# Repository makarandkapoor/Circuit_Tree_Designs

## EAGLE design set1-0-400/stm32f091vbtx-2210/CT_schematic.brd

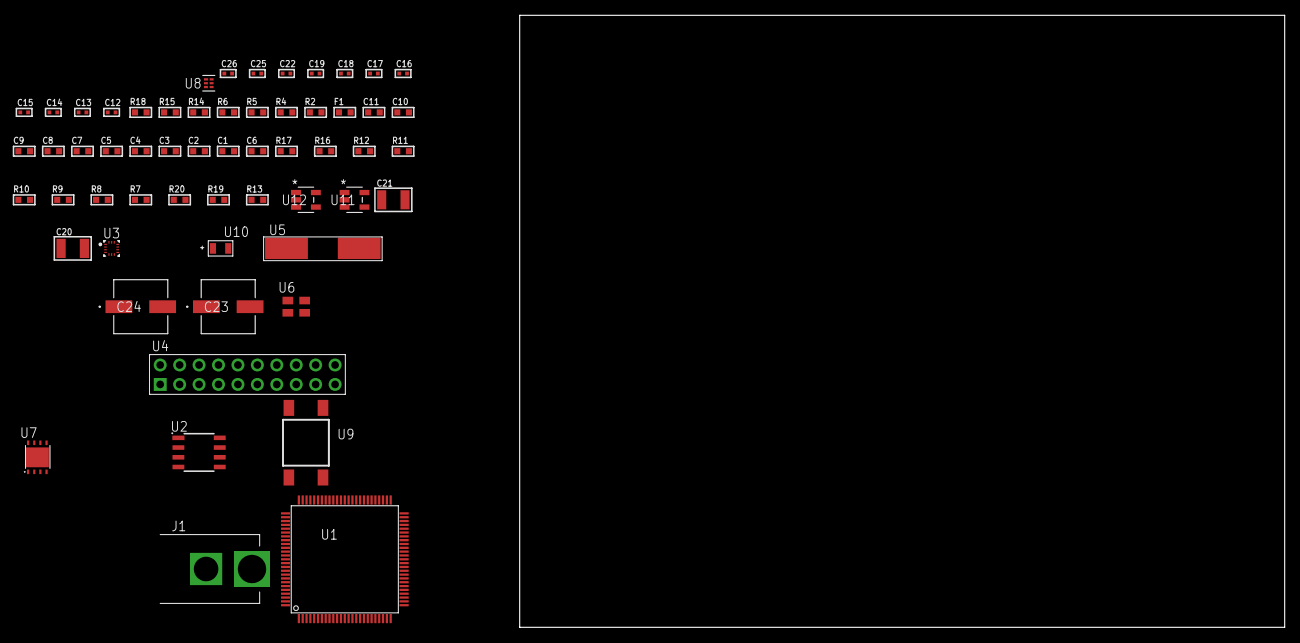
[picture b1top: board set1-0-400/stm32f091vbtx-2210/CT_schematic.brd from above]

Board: 2 copper layers, 100.0 x 80.0 mm, 58 parts (0 on the bottom side), 28 nets, no tracks yet.

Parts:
C1, C11: 1e-06; C0603
C2, C3, C4, C5, C7, C8, C9: 1e-07; C0603
C6: 4.7e-06; C0603
C10: 1e-08; C0603
C12, C13: 1e-11; C0402
C14, C18, C19, C25, C26: 1e-08; C0402
C15, C16, C17, C22: 1e-07; C0402
C20, C21: 1e-05; C1210
C23, C24: 0.0001; EXV-9H
F1: 240.0; L0603
J1: PJ-037B; PJ-037B_PACKAGE
R2, R15: 1000.0; R0603
R4: 4700.0; R0603
R5, R6: 2200.0; R0603
R7, R8, R9, R10, R11, R12, R16, R17: 10000.0; R0603
R13: 100000.0; R0603
R14: 2231.0; R0603
R18: 9100.0; R0603
R19: 680000.0; R0603
R20: 120000.0; R0603
U1: stm32f091vbt6; LQFP100
U2: AT25512N-SH-T; SOIC-8
U3: BMC150; LGA14R35P5X6_200X200X100
U4: TST-110-05-T-D-RA
U5: ABLS-25.000MHZ-B2F-T
U6: ASEK-32.768KHz-ECST; ASEK
U7: LP3878SDX-ADJ/NOPB; WSON-8
U8: TPS3895ADRYR; SON-6
U9: 4-1437565-2; SW_4-1437565-2
U10: Q65110A2395; LGM67K-G1J2-24-Z
U11, U12: nc7sz125m5x; NC7SZ125M5X

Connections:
CLK_CRYSTAL_U1_12: C12.1, U1.12, U5.1
CLK_CRYSTAL_U1_13: C13.1, U1.13, U5.2
CLK_U1_8: U1.8, U6.3
GND: C1.2, C2.2, C3.2, C4.2, C5.2, C6.2, C7.2, C8.2, C9.2, C10.2, C11.2, C12.2, C13.2, C14.2, C15.2, C16.2, C17.2, C18.2, C19.2, C20.2, C21.2, C22.2, C23.2, C24.2, C25.2, C26.2, J1.2, R2.2, R7.2, R15.2, R18.2, R20.2, U1.20, U1.27, U1.49, U1.74, U1.99, U2.4, U3.1, U3.6, U3.7, U3.9, U4.4, U4.6, U4.8, U4.10, U4.12, U4.14, U4.16, U4.18, U4.20, U6.2, U7.3, U7.PAD, U8.2, U10.C, U11.2, U11.3, U12.1, U12.3
NET_U1_14: R4.1, U1.14, U12.4
NET_U1_21: C10.1, C11.1, F1.1, U1.21
NET_U1_68: R5.1, U1.68, U3.11
NET_U1_69: R6.1, U1.69, U3.14
NET_U1_94: R7.1, U1.94
NET_U1_98: U9.3, U9.4
NET_U2_3: R8.1, U2.3
NET_U2_7: R10.1, U2.7
NET_U7_1: C19.1, U7.1
NET_U7_6: R14.2, R15.1, U7.6
NET_U7_8: R13.1, U7.8
NET_U8_1: R17.1, R18.1, U8.1
NET_U8_3: R19.2, R20.1, U8.3
NET_U8_4: R16.1, U8.4, U11.4, U12.2
NET_U9_1: R2.1, U9.1, U9.2
PROC_SPI1_MISO: U1.31, U2.2
PROC_SPI1_MOSI: U1.32, U2.5
PROC_SPI1_NSS: R9.1, U1.29, U2.1
PROC_SPI1_SCK: U1.30, U2.6
PROC_SYS_SWCLK: U1.76, U4.9
PROC_SYS_SWDIO: U1.72, U4.7
RST_OUT_U4_SRESET_B: R12.1, U4.15, U11.1
VCC_S1_14V6: C20.1, C23.1, C24.1, J1.1, R13.2, U7.4
VCC_TIER1_3V3: C1.1, C2.1, C3.1, C4.1, C5.1, C6.1, C7.1, C8.1, C9.1, C14.1, C15.1, C16.1, C17.1, C18.1, C21.1, C22.1, C25.1, C26.1, F1.2, R4.2, R5.2, R6.2, R8.2, R9.2, R10.2, R11.1, R11.2, R12.2, R14.1, R16.2, R17.2, R19.1, U1.6, U1.28, U1.50, U1.75, U1.100, U2.8, U3.8, U3.10, U3.12, U3.13, U4.1, U6.4, U7.5, U8.6, U11.5, U12.5

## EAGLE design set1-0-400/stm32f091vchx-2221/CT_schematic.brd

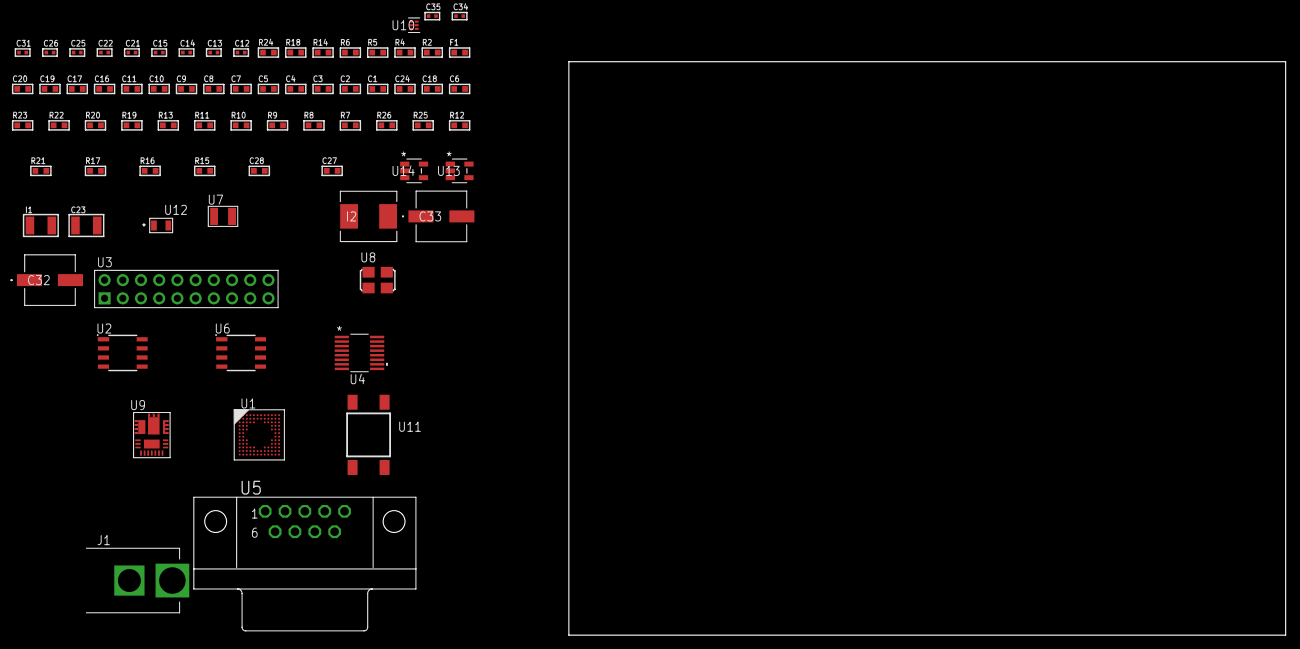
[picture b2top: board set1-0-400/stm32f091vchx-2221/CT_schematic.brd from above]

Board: 2 copper layers, 100.0 x 80.0 mm, 75 parts (0 on the bottom side), 45 nets, no tracks yet.

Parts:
C1, C11, C16, C17, C19, C20: 1e-06; C0603
C2, C3, C4, C5, C7, C8, C9: 1e-07; C0603
C6: 4.7e-06; C0603
C10: 1e-08; C0603
C12, C13: 1e-11; C0402
C14, C21, C22, C34, C35: 1e-08; C0402
C15, C25, C26, C31: 1e-07; C0402
C18: 2.2e-07; C0603
C23: 0.0001; C1210
C24: 2.2e-06; C0603
C27: 8.6971073877236e-09; R0603
C28: 2.9649229730876e-07; R0603
C32, C33: 0.0001; EXV-9H
F1: 240.0; L0603
I1: 1e-05; L1210
I2: 6.8e-07; IND25X25CZ
J1: PJ-037B; PJ-037B_PACKAGE
R2: 1000.0; R0603
R4: 4700.0; R0603
R5, R6: 2200.0; R0603
R7, R8, R9, R10, R11, R13, R22, R23: 10000.0; R0603
R12: 100000.0; R0603
R14: 0.1; R0603
R15: 4030.2416170974; R0603
R16: 719.68600305311; R0603
R17: 58.613333333333; R0603
R18: 130.0; R0603
R19: 39000.0; R0603
R20: 49900.0; R0603
R21: 5147.5789473684; R0603
R24: 9100.0; R0603
R25: 680000.0; R0603
R26: 120000.0; R0603
U1: stm32f091vch6; UFBGA100
U2: AT25M01-SSHM-T; SOIC-8
U3: TST-110-05-T-D-RA
U4: LTC2804CGN-1#PBF; SSOP-16
U5: 182-009-113R531; 182-009-MALE
U6: M24M02-DRMN6TP; SOIC-8
U7: ABS07-32.768KHZ-7-T
U8: ASFL1-25MHZ-NCS; ASFL1
U9: IR3899MTR1PBF
U10: TPS3895ADRYR; SON-6
U11: 4-1437565-2; SW_4-1437565-2
U12: Q65110A2395; LGM67K-G1J2-24-Z
U13, U14: nc7sz125m5x; NC7SZ125M5X

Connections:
CLK_CRYSTAL_U1_D1: C12.1, U1.D1, U7.1
CLK_CRYSTAL_U1_E1: C13.1, U1.E1, U7.2
CLK_U1_F1: U1.F1, U8.3
GND: C1.2, C2.2, C3.2, C4.2, C5.2, C6.2, C7.2, C8.2, C9.2, C10.2, C11.2, C12.2, C13.2, C14.2, C15.2, C16.2, C17.2, C19.2, C20.2, C21.2, C22.2, C24.2, C25.2, C26.2, C31.2, C32.2, C33.2, C34.2, C35.2, J1.2, R2.2, R7.2, R13.2, R14.1, R14.2, R16.2, R19.2, R21.2, R24.2, R26.2, U1.D3, U1.F11, U1.F12, U1.K1, U2.4, U3.4, U3.6, U3.8, U3.10, U3.12, U3.14, U3.16, U3.18, U3.20, U4.8, U5.5, U6.4, U8.2, U9.4, U9.11, U9.17, U10.2, U12.C, U13.2, U13.3, U14.1, U14.3
NET_U1_A3: R5.1, U1.A3, U6.6
NET_U1_A4: R7.1, U1.A4
NET_U1_B3: R6.1, U1.B3, U6.5
NET_U1_H2: R4.1, U1.H2, U14.4
NET_U1_M1: C10.1, C11.1, F1.1, U1.M1
NET_U1_M12: U11.3, U11.4
NET_U2_3: R8.1, U2.3
NET_U2_7: R10.1, U2.7
NET_U4_6: C16.1, U4.6
NET_U4_7: C18.1, I1.2, U4.7
NET_U4_9: C17.1, U4.9
NET_U4_10: C18.2, U4.10
NET_U4_11: R12.1, U4.11
NET_U5_2: U4.1, U5.2
NET_U5_3: U4.3, U5.3
NET_U5_7: U4.2, U5.7
NET_U5_8: U4.4, U5.8
NET_U6_3: R13.1, U6.3
NET_U9_1: C27.1, R15.1, R16.1, R17.1, R18.1, U9.1, U9.8
NET_U9_2: C26.1, U9.2
NET_U9_3: C27.2, C28.1, C28.2, U9.3
NET_U9_5: R19.1, U9.5
NET_U9_10: C24.1, U9.10
NET_U9_12: C23.1, I2.1, U9.12
NET_U9_14: C23.2, U9.14
NET_U9_15: R20.1, R21.1, U9.15
NET_U9_ATNET_3: I2.2, R15.2
NET_U9_ATNET_4: C28.2, R17.2
NET_U10_1: R23.1, R24.1, U10.1
NET_U10_3: R25.2, R26.1, U10.3
NET_U10_4: R22.1, U10.4, U13.4, U14.2
NET_U11_1: R2.1, U11.1, U11.2
PROC_SPI1_MISO: U1.A7, U2.2
PROC_SPI1_MOSI: U1.C5, U2.5
PROC_SPI1_NSS: R9.1, U1.A9, U2.1
PROC_SPI1_SCK: U1.A8, U2.6
PROC_SYS_SWCLK: U1.A10, U3.9
PROC_SYS_SWDIO: U1.A11, U3.7
RST_OUT_U3_SRESET_B: R11.1, U3.15, U13.1
VCC_S1_16V8: C25.1, C32.1, C33.1, J1.1, R20.2, U9.9
VCC_TIER1_3V3: C1.1, C2.1, C3.1, C4.1, C5.1, C6.1, C7.1, C8.1, C9.1, C14.1, C15.1, C19.1, C20.1, C21.1, C22.1, C31.1, C34.1, C35.1, F1.2, I1.1, I2.2, R4.2, R5.2, R6.2, R8.2, R9.2, R10.2, R11.2, R12.2, R15.2, R22.2, R23.2, R25.1, U1.C4, U1.E2, U1.G11, U1.G12, U1.H3, U2.8, U3.1, U4.5, U4.12, U6.8, U8.4, U10.6, U13.5, U14.5

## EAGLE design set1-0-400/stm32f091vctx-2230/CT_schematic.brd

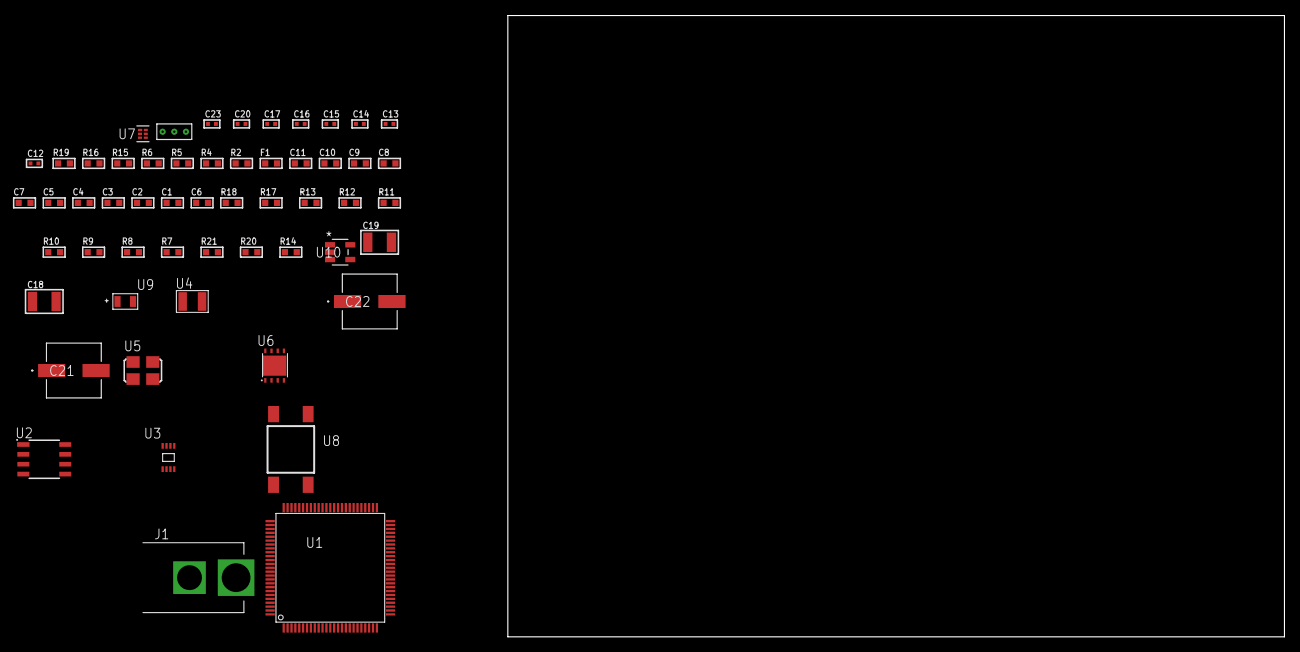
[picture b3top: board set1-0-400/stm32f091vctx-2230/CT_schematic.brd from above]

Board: 2 copper layers, 100.0 x 80.0 mm, 55 parts (0 on the bottom side), 30 nets, no tracks yet.

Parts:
C1, C11: 1e-06; C0603
C2, C3, C4, C5, C7, C8, C9: 1e-07; C0603
C6: 4.7e-06; C0603
C10: 1e-08; C0603
C12, C13: 1e-11; C0402
C14, C15, C16, C17, C23: 1e-08; C0402
C18, C19: 1e-05; C1210
C20: 1e-07; C0402
C21, C22: 0.0001; EXV-9H
F1: 240.0; L0603
J1: PJ-037B; PJ-037B_PACKAGE
R2, R16: 1000.0; R0603
R4: 4700.0; R0603
R5, R6: 2200.0; R0603
R7, R8, R9, R10, R11, R12, R13, R17, R18: 10000.0; R0603
R14: 100000.0; R0603
R15: 2231.0; R0603
R19: 9100.0; R0603
R20: 680000.0; R0603
R21: 120000.0; R0603
U1: stm32f091vct6; LQFP100
U2: AT25160B-SSHL-T; SOIC-8
U3: 24AA32AT-I/MNY; TDFN-8/6MM
U4: ABS07-32.768KHZ-7-T
U5: ASFL1-25MHZ-NCS; ASFL1
U6: LP3878SDX-ADJ/NOPB; WSON-8
U7: TPS3895ADRYR; SON-6
U8: 4-1437565-2; SW_4-1437565-2
U9: Q65110A2395; LGM67K-G1J2-24-Z
U10: nc7sz125m5x; NC7SZ125M5X
U11: Dummy; DUMMY_PACKAGE_119

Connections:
CLK_CRYSTAL_U1_8: C12.1, U1.8, U4.1
CLK_CRYSTAL_U1_9: C13.1, U1.9, U4.2
CLK_U1_12: U1.12, U5.3
GND: C1.2, C2.2, C3.2, C4.2, C5.2, C6.2, C7.2, C8.2, C9.2, C10.2, C11.2, C12.2, C13.2, C14.2, C15.2, C16.2, C17.2, C18.2, C19.2, C20.2, C21.2, C22.2, C23.2, J1.2, R2.2, R7.2, R11.2, R13.2, R16.2, R19.2, R21.2, U1.20, U1.27, U1.49, U1.74, U1.99, U2.4, U3.4, U3.7, U5.2, U6.3, U6.PAD, U7.2, U9.C, U10.1, U10.3, U11.1
NET_U1_13: R5.1, U1.13, U3.6
NET_U1_14: R4.1, U1.14, U10.4
NET_U1_21: C10.1, C11.1, F1.1, U1.21
NET_U1_69: R6.1, U1.69, U3.5
NET_U1_94: R7.1, U1.94
NET_U1_98: U8.3, U8.4
NET_U2_3: R8.1, U2.3
NET_U2_7: R10.1, U2.7
NET_U3_1: R11.1, U3.1
NET_U3_2: R12.1, U3.2
NET_U3_3: R13.1, U3.3
NET_U6_1: C17.1, U6.1
NET_U6_6: R15.2, R16.1, U6.6
NET_U6_8: R14.1, U6.8
NET_U7_1: R18.1, R19.1, U7.1
NET_U7_3: R20.2, R21.1, U7.3
NET_U7_4: R17.1, U7.4, U10.2
NET_U8_1: R2.1, U8.1, U8.2
PROC_ADC_IN3: U1.26, U11.3
PROC_ADC_IN13: U1.18, U11.2
PROC_SPI1_MISO: U1.31, U2.2
PROC_SPI1_MOSI: U1.32, U2.5
PROC_SPI1_NSS: R9.1, U1.29, U2.1
PROC_SPI1_SCK: U1.30, U2.6
VCC_S1_14V2: C18.1, C21.1, C22.1, J1.1, R14.2, U6.4
VCC_TIER1_3V3: C1.1, C2.1, C3.1, C4.1, C5.1, C6.1, C7.1, C8.1, C9.1, C14.1, C15.1, C16.1, C19.1, C20.1, C23.1, F1.2, R4.2, R5.2, R6.2, R8.2, R9.2, R10.2, R12.2, R15.1, R17.2, R18.2, R20.1, U1.6, U1.28, U1.50, U1.75, U1.100, U2.8, U3.8, U5.4, U6.5, U7.6, U10.5

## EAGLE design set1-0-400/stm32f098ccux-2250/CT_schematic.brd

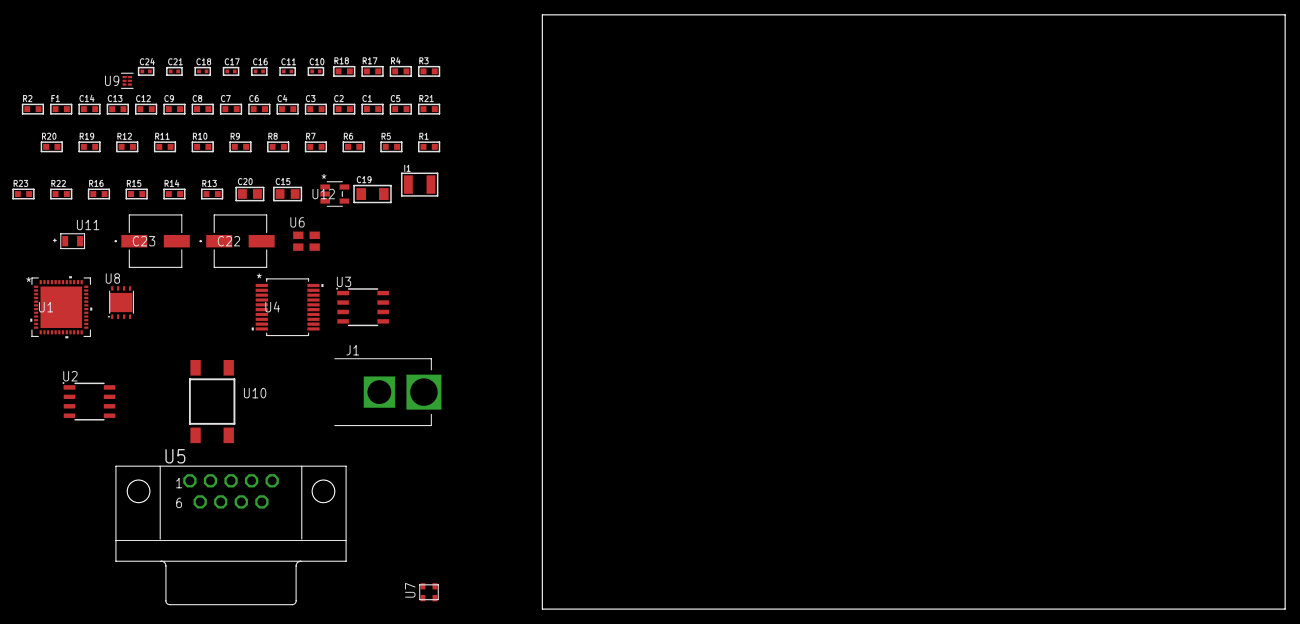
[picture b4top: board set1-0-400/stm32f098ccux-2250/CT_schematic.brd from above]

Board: 2 copper layers, 100.0 x 80.0 mm, 62 parts (0 on the bottom side), 46 nets, no tracks yet.

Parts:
C1, C9, C12, C13, C14: 1e-06; C0603
C2, C3, C4, C6, C7: 1e-07; C0603
C5: 4.7e-06; C0603
C8: 1e-08; C0603
C10, C11, C16, C17, C18, C24: 1e-08; C0402
C15: 4.7e-06; C0805
C19: 1e-05; C1206
C20: 1e-05; C0805
C21: 1e-07; C0402
C22, C23: 0.0001; EXV-9H
F1: 240.0; L0603
I1: 1.5e-05; L1210
J1: PJ-037B; PJ-037B_PACKAGE
R1, R5, R6, R7, R8, R9, R10, R11, R12, R19, R20: 10000.0; R0603
R2, R18: 1000.0; R0603
R3: 910.0; R0603
R4: 4700.0; R0603
R13, R14, R15, R16: 100000.0; R0603
R17: 806.0; R0603
R21: 82000.0; R0603
R22: 300000.0; R0603
R23: 120000.0; R0603
U1: stm32f098ccu6; UFQFPN48
U2: AT25010B-SSHL-T; SOIC-8
U3: AT25128B-SSHL-T; SOIC-8
U4: MAX3218EAP+T; SSOP-20
U5: 182-009-113R531; 182-009-MALE
U6: ASEK-2-32.768KHz-ECST; ASEK
U7: ASDMB-25.000MHZ-EC-T; ASDMB-XX.XXXXMHZ-XX-XX-XXX
U8: LP3878SDX-ADJ/NOPB; WSON-8
U9: TPS3895ADRYR; SON-6
U10: 4-1437565-2; SW_4-1437565-2
U11: Q65110A2395; LGM67K-G1J2-24-Z
U12: nc7sz125m5x; NC7SZ125M5X

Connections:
CLK_U1_3: U1.3, U6.3
CLK_U1_5: U1.5, U7.3
GND: C1.2, C2.2, C3.2, C4.2, C5.2, C6.2, C7.2, C8.2, C9.2, C10.2, C11.2, C12.2, C13.2, C14.2, C16.2, C17.2, C18.2, C19.2, C20.2, C21.2, C22.2, C23.2, C24.2, J1.2, R2.2, R5.2, R6.2, R18.2, R21.2, R23.2, U1.8, U1.23, U1.35, U1.47, U1.49, U2.4, U3.4, U4.5, U4.17, U4.20, U5.5, U6.2, U7.2, U8.3, U8.PAD, U9.2, U11.C, U12.1, U12.3
NET_U1_7: R4.1, U1.7, U12.4
NET_U1_9: C8.1, C9.1, F1.1, U1.9
NET_U1_20: R6.1, U1.20
NET_U1_44: R5.1, U1.44
NET_U1_45: R3.1, U1.45, U11.A
NET_U1_46: R1.1, U1.46, U10.3, U10.4
NET_U2_3: R7.1, U2.3
NET_U2_7: R9.1, U2.7
NET_U3_3: R10.1, U3.3
NET_U3_7: R12.1, U3.7
NET_U4_1: I1.1, U4.1
NET_U4_2: R13.1, U4.2
NET_U4_3: R14.1, U4.3
NET_U4_4: R15.1, U4.4
NET_U4_15: C14.1, U4.15
NET_U4_16: C15.2, U4.16
NET_U4_18: C15.1, U4.18
NET_U4_19: C13.1, U4.19
NET_U5_2: U4.12, U5.2
NET_U5_3: U4.14, U5.3
NET_U5_7: U4.11, U5.7
NET_U5_8: U4.13, U5.8
NET_U8_1: C18.1, U8.1
NET_U8_6: R17.2, R18.1, U8.6
NET_U8_8: R16.1, U8.8
NET_U9_1: R20.1, R21.1, U9.1
NET_U9_3: R22.2, R23.1, U9.3
NET_U9_4: R19.1, U9.4, U12.2
NET_U10_1: R2.1, U10.1, U10.2
PROC_SPI1_MISO: U1.16, U2.2
PROC_SPI1_MOSI: U1.17, U2.5
PROC_SPI1_NSS: R8.1, U1.14, U2.1
PROC_SPI1_SCK: U1.15, U2.6
PROC_SPI2_MISO: U1.27, U3.2
PROC_SPI2_MOSI: U1.28, U3.5
PROC_SPI2_NSS: R11.1, U1.25, U3.1
PROC_SPI2_SCK: U1.21, U3.6
PROC_USART1_CTS: U1.32, U4.8
PROC_USART1_RTS: U1.33, U4.10
PROC_USART1_RX: U1.31, U4.9
PROC_USART1_TX: U1.30, U4.7
VCC_S1_7V0: C19.1, C22.1, C23.1, J1.1, R16.2, U8.4
VCC_TIER1_1V8: C1.1, C2.1, C3.1, C4.1, C5.1, C6.1, C7.1, C10.1, C11.1, C12.1, C16.1, C17.1, C20.1, C21.1, C24.1, F1.2, I1.2, R1.2, R3.2, R4.2, R7.2, R8.2, R9.2, R10.2, R11.2, R12.2, R13.2, R14.2, R15.2, R17.1, R19.2, R20.2, R22.1, U1.1, U1.24, U1.36, U1.48, U2.8, U3.8, U4.6, U6.4, U7.4, U8.5, U9.6, U12.5

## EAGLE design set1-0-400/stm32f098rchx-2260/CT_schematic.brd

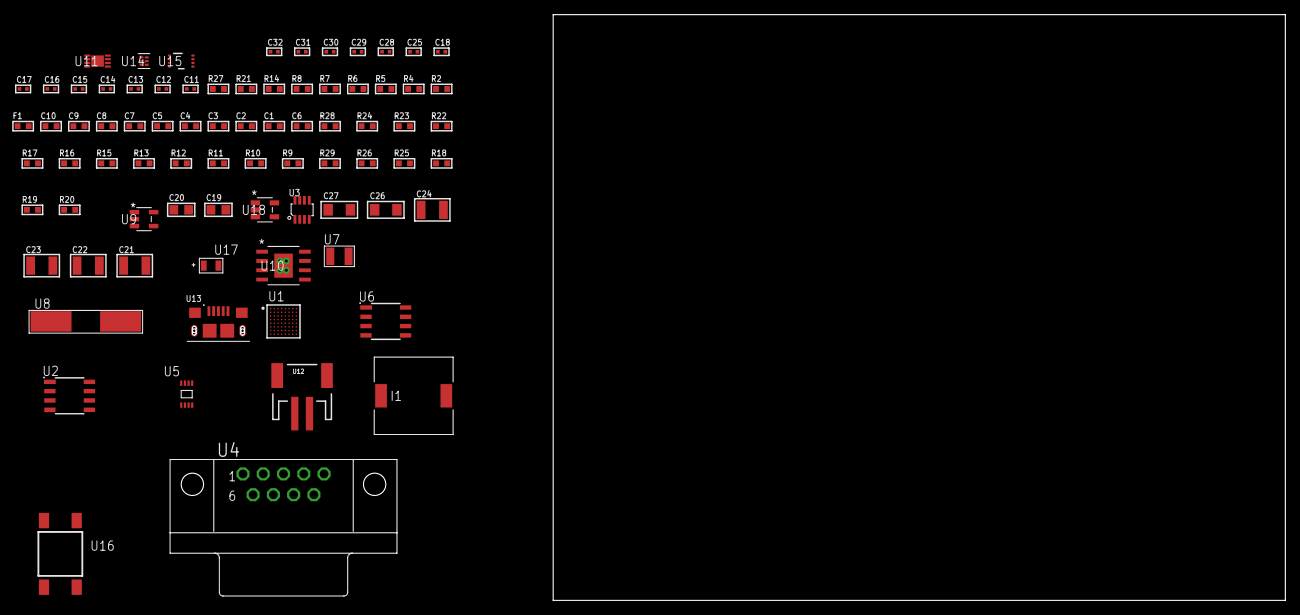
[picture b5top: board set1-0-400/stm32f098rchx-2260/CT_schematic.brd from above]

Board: 2 copper layers, 79 parts (0 on the bottom side), 43 nets, no tracks yet.

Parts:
C1, C10: 1e-06; C0603
C2, C3, C4, C5, C7, C8: 1e-07; C0603
C6: 4.7e-06; C0603
C9: 1e-08; C0603
C11, C12, C13, C14: 1e-11; C0402
C15, C17, C18, C28, C30, C32: 1e-08; C0402
C16, C25, C29, C31: 1e-07; C0402
C19, C20: 1e-05; C0805
C21, C22, C23, C24: 1e-05; C1210
C26, C27: 1e-05; C1206
F1: 240.0; L0603
I1: 5.2e-06; DR1040
R2: 1000.0; R0603
R4: 4700.0; R0603
R5, R6, R7, R8, R21: 2200.0; R0603
R9, R10, R11, R12, R13, R15, R16, R17, R22, R23, R28: 10000.0; R0603
R14: 120.0; R0603
R18: 490000.0; R0603
R19: 1000000.0; R0603
R20: 4031.5447154472; R0603
R24: 82000.0; R0603
R25: 300000.0; R0603
R26: 120000.0; R0603
R27: 2000.0; R0603
R29: 200000.0; R0603
U1: stm32f098rch7; UFBGA64
U2: AT25128B-SSHL-T; SOIC-8
U3: MAX3051EKA+T; SOT-23-8
U4: 182-009-113R531; 182-009-MALE
U5: 24AA08T-I/MNY; TDFN-8/6MM
U6: 24AA1025T-I/SN; SOIC-8
U7: ABS07-32.768KHZ-7-T
U8: ABLS-25.000MHZ-B2F-T
U9: ltc3406es5; TSOT-23-5
U10: MIC5234YME; SOIC-8_EP
U11: MCP73831T-2ACI/MC; DFN8_2X3MC
U12: S2B-PH-SM4-TB(LF)(SN); JST-2-SMD
U13: 10118193-0001LF; FCI_10118193-0001LF
U14: TPS3895ADRYR; SON-6
U15: LSF0102DCTR; DCU0008A_N
U16: 4-1437565-2; SW_4-1437565-2
U17: Q65110A2395; LGM67K-G1J2-24-Z
U18: nc7sz125m5x; NC7SZ125M5X

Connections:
CLK_CRYSTAL_U1_A1: C11.1, U1.A1, U7.1
CLK_CRYSTAL_U1_B1: C12.1, U1.B1, U7.2
CLK_CRYSTAL_U1_C1: C13.1, U1.C1, U8.1
CLK_CRYSTAL_U1_D1: C14.1, U1.D1, U8.2
GND: C1.2, C2.2, C3.2, C4.2, C5.2, C6.2, C7.2, C8.2, C9.2, C10.2, C11.2, C12.2, C13.2, C14.2, C15.2, C16.2, C17.2, C18.2, C19.2, C20.1, C20.2, C21.2, C22.2, C23.2, C24.2, C25.2, C26.2, C27.2, C28.2, C29.2, C30.2, C31.2, C32.2, R2.2, R9.2, R10.2, R16.2, R18.2, R21.2, R24.2, R26.2, R27.2, U1.C2, U1.D4, U1.D5, U1.D6, U1.F1, U2.4, U3.2, U3.8, U4.5, U5.4, U5.7, U6.4, U6.7, U9.2, U10.7, U10.EPAD, U11.6, U11.9, U12.2, U13.5, U13.6, U13.7, U13.8, U13.9, U14.2, U15.1, U17.C, U18.1, U18.3
INPUT_USBPOWER_5V: C26.1, R28.2, U11.1, U11.2, U13.1
NET_U1_B4: R9.1, U1.B4
NET_U1_B8: R8.1, U1.B8, U6.5
NET_U1_C3: R6.1, U1.C3, U5.5
NET_U1_C7: R5.1, U1.C7, U5.6
NET_U1_C8: R7.1, U1.C8, U6.6
NET_U1_E1: R4.1, U1.E1, U18.4
NET_U1_G6: R10.1, U1.G6
NET_U1_H1: C9.1, C10.1, F1.1, U1.H1
NET_U1_H8: U16.3, U16.4
NET_U2_3: R11.1, U2.3
NET_U2_7: R13.1, U2.7
NET_U3_6: R14.2, U3.6
NET_U4_2: R14.2, U3.6, U4.2
NET_U4_3: R14.1, U3.7, U4.3
NET_U6_1: R16.1, U6.1
NET_U6_2: R17.1, U6.2
NET_U6_3: R15.1, U6.3
NET_U9_3: I1.1, U9.3
NET_U9_5: R18.1, R19.1, U9.5
NET_U9_ATNET_3: I1.2, R19.2
NET_U10_4: R20.2, R21.1, U10.4
NET_U11_5: R28.1, U11.5
NET_U11_8: R27.1, U11.8
NET_U14_1: R23.1, R24.1, U14.1
NET_U14_3: R25.2, R26.1, U14.3
NET_U14_4: R22.1, U14.4, U18.2
NET_U15_8: R29.1, U15.8
NET_U16_1: R2.1, U16.1, U16.2
PROC_CAN_RX_TOXCVR: U3.4, U15.5
PROC_CAN_TX_TOXCVR: U3.1, U15.6
PROC_SPI1_MISO: U1.A4, U2.2
PROC_SPI1_MOSI: U1.C4, U2.5
PROC_SPI1_NSS: R12.1, U1.A6, U2.1
PROC_SPI1_SCK: U1.A5, U2.6
VCC_S1_3V7: C19.1, C21.1, C22.1, C27.1, U9.4, U10.5, U10.8, U11.3, U11.4, U12.1
VCC_TIER1_1V8: C1.1, C2.1, C3.1, C4.1, C5.1, C6.1, C7.1, C8.1, C15.1, C17.1, C18.1, C20.2, C25.1, C30.1, C31.1, C32.1, F1.2, I1.2, R4.2, R5.2, R6.2, R7.2, R8.2, R11.2, R12.2, R13.2, R15.2, R17.2, R19.2, R22.2, R23.2, R25.1, U1.B2, U1.D2, U1.E4, U1.E5, U1.E6, U2.8, U5.8, U6.8, U14.6, U15.2, U18.5
VCC_TIER1_3V3: C16.1, C23.1, C24.1, C28.1, C29.1, R20.1, R29.2, U3.3, U10.1, U15.7

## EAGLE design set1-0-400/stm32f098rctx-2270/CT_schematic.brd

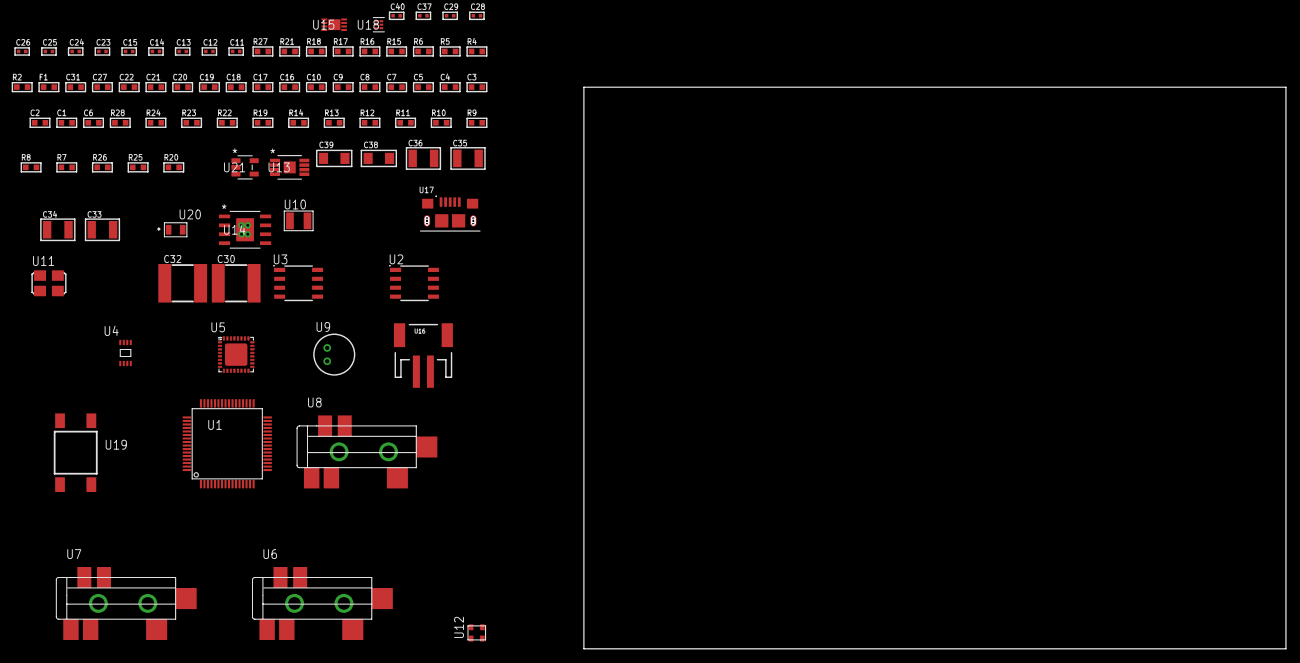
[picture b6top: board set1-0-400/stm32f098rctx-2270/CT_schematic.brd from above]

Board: 2 copper layers, 122.6 x 80.0 mm, 88 parts (0 on the bottom side), 52 nets, no tracks yet.

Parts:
C1, C10, C16, C17, C18, C19, C20, C21, C22, C27, C31: 1e-06; C0603
C2, C3, C4, C5, C7, C8: 1e-07; C0603
C6: 4.7e-06; C0603
C9: 1e-08; C0603
C11, C12: 1e-11; C0402
C13, C14, C15, C28, C29, C40: 1e-08; C0402
C23, C24, C25, C26, C37: 1e-07; C0402
C30, C32: 6.8e-05; 2220
C33, C34, C35, C36: 1e-05; C1210
C38, C39: 1e-05; C1206
F1: 240.0; L0603
R2: 1000.0; R0603
R4: 4700.0; R0603
R5, R6, R18, R21: 2200.0; R0603
R7, R8, R9, R10, R11, R12, R13, R14, R19, R22, R23, R28: 10000.0; R0603
R15, R16: 1270.0; R0603
R17: 3900.0; R0603
R20: 4031.5447154472; R0603
R24: 82000.0; R0603
R25: 300000.0; R0603
R26: 120000.0; R0603
R27: 2000.0; R0603
U1: stm32f098rct7; LQFP64
U2: AT25010B-SSHL-T; SOIC-8
U3: AT25160B-SSHL-T; SOIC-8
U4: 24AA02T-I/MNY; TDFN-8/6MM
U5: SGTL5000XNAA3; QFN-32
U6, U7, U8: SJ-43515TS-SMT-TR
U9: WM-64PCT; WM-64PC
U10: ABS07-32.768KHZ-7-T
U11: ASFL-24.57MHZ-NCS; ASFL1
U12: ASDMB-25.000MHZ-EC-T; ASDMB-XX.XXXXMHZ-XX-XX-XXX
U13: MIC47100YMME; MSOP-8_EP
U14: MIC5234YME; SOIC-8_EP
U15: MCP73831T-2ACI/MC; DFN8_2X3MC
U16: S2B-PH-SM4-TB(LF)(SN); JST-2-SMD
U17: 10118193-0001LF; FCI_10118193-0001LF
U18: TPS3895ADRYR; SON-6
U19: 4-1437565-2; SW_4-1437565-2
U20: Q65110A2395; LGM67K-G1J2-24-Z
U21: nc7sz125m5x; NC7SZ125M5X

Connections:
CLK_CRYSTAL_U1_3: C11.1, U1.3, U10.1
CLK_CRYSTAL_U1_4: C12.1, U1.4, U10.2
CLK_U1_5: U1.5, U12.3
CLK_U5_21: U5.21, U11.3
GND: C1.2, C2.2, C3.2, C4.2, C5.2, C6.2, C7.2, C8.2, C9.2, C10.2, C11.2, C12.2, C13.2, C14.2, C15.2, C23.2, C24.2, C25.2, C26.2, C27.2, C28.2, C29.2, C30.2, C31.2, C32.2, C33.2, C34.2, C35.2, C36.2, C37.2, C38.2, C39.2, C40.2, R2.2, R7.2, R8.2, R16.2, R18.2, R21.2, R24.2, R26.2, R27.2, U1.12, U1.18, U1.31, U1.47, U1.63, U2.4, U3.4, U4.4, U5.1, U5.3, U5.7, U5.EXP, U7.1, U8.1, U9.2, U11.2, U12.2, U13.3, U13.EPAD, U14.7, U14.EPAD, U15.6, U15.9, U16.2, U17.5, U17.6, U17.7, U17.8, U17.9, U18.2, U20.C, U21.1, U21.3
INPUT_USBPOWER_5V: C38.1, R28.2, U15.1, U15.2, U17.1
NET_U1_6: R5.1, U1.6, U4.6
NET_U1_7: R4.1, U1.7, U21.4
NET_U1_13: C9.1, C10.1, F1.1, U1.13
NET_U1_28: R8.1, U1.28
NET_U1_43: R6.1, U1.43, U4.5
NET_U1_60: R7.1, U1.60
NET_U1_62: U19.3, U19.4
NET_U2_3: R9.1, U2.3
NET_U2_7: R11.1, U2.7
NET_U3_3: R12.1, U3.3
NET_U3_7: R14.1, U3.7
NET_U5_10: C26.1, U5.10
NET_U5_29: R15.1, U5.29
NET_U5_31: R16.1, U5.31
NET_U6_1: U5.4, U6.1
NET_U6_2: U5.2, U6.2
NET_U6_5: U5.6, U6.5
NET_U7_2: C17.1, U7.2
NET_U7_5: C16.1, U7.5
NET_U8_2: C19.1, C20.1, U8.2
NET_U8_5: C18.1, U8.5
NET_U8_13: C19.2, C20.2
NET_U9_1: C21.1, C22.1, C27.1, U5.16, U9.1
NET_U9_15: C21.2, C22.2
NET_U13_6: R17.2, R18.1, U13.6
NET_U14_4: R20.2, R21.1, U14.4
NET_U15_5: R28.1, U15.5
NET_U15_8: R27.1, U15.8
NET_U18_1: R23.1, R24.1, U18.1
NET_U18_3: R25.2, R26.1, U18.3
NET_U18_4: R22.1, U18.4, U21.2
NET_U19_1: R2.1, U19.1, U19.2
PROC_I2S1_CK: U1.55, U5.24
PROC_I2S1_SD: U1.57, U5.26
PROC_I2S1_WS: U1.50, U5.23
PROC_SPI1_MISO: U1.22, U3.2
PROC_SPI1_MOSI: U1.23, U3.5
PROC_SPI1_NSS: R13.1, U1.20, U3.1
PROC_SPI1_SCK: U1.21, U3.6
PROC_SPI2_MISO: U1.10, U2.2
PROC_SPI2_MOSI: U1.11, U2.5
PROC_SPI2_NSS: R10.1, U1.33, U2.1
PROC_SPI2_SCK: U1.29, U2.6
VCC_S1_3V7: C30.1, C31.1, C33.1, C34.1, C39.1, R19.1, R19.2, U13.1, U13.2, U13.4, U13.5, U14.5, U14.8, U15.3, U15.4, U16.1
VCC_TIER1_1V8: C1.1, C2.1, C3.1, C4.1, C5.1, C6.1, C7.1, C8.1, C13.1, C14.1, C15.1, C23.1, C24.1, C25.1, C29.1, C32.1, C37.1, C40.1, F1.2, R4.2, R5.2, R6.2, R9.2, R10.2, R11.2, R12.2, R13.2, R14.2, R15.2, R17.1, R22.2, R23.2, R25.1, U1.1, U1.19, U1.32, U1.48, U1.64, U2.8, U3.8, U4.7, U4.8, U5.5, U5.20, U5.30, U12.4, U13.7, U13.8, U18.6, U21.5
VCC_TIER1_3V3: C28.1, C35.1, C36.1, R20.1, U11.4, U14.1

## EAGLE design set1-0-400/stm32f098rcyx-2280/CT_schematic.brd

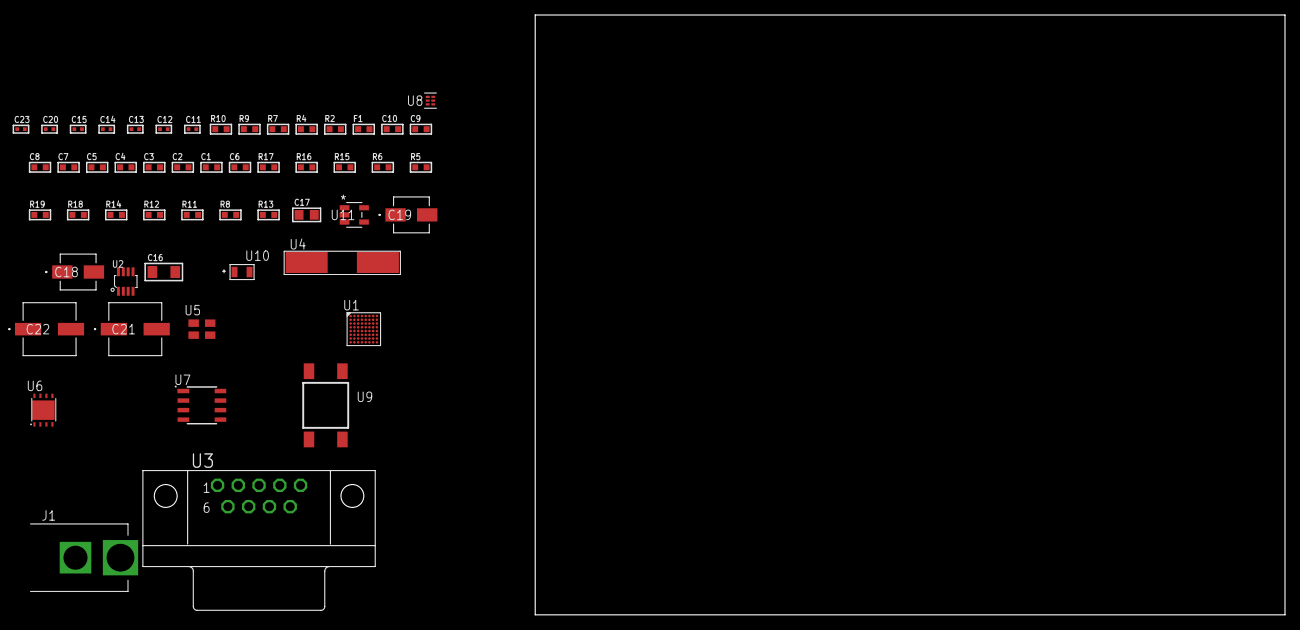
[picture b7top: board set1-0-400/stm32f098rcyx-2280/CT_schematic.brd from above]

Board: 2 copper layers, 100.0 x 80.0 mm, 53 parts (0 on the bottom side), 27 nets, no tracks yet.

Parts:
C1, C10: 1e-06; C0603
C2, C3, C4, C5, C7, C8: 1e-07; C0603
C6: 4.7e-06; C0603
C9: 1e-08; C0603
C11, C12: 1e-11; C0402
C13, C20: 1e-07; C0402
C14, C15, C23: 1e-08; C0402
C16: 1e-05; C1206
C17: 1e-05; C0805
C18: 1e-06; EXV-9B
C19: 2.2e-06; EXV-9B
C21, C22: 0.0001; EXV-9H
F1: 240.0; L0603
J1: PJ-037B; PJ-037B_PACKAGE
R2, R10: 1000.0; R0603
R4: 4700.0; R0603
R5, R6, R15, R16: 10000.0; R0603
R7: 120.0; R0603
R8, R11, R12, R14: 100000.0; R0603
R9: 806.0; R0603
R13: 164658.62; R0603
R17: 82000.0; R0603
R18: 300000.0; R0603
R19: 120000.0; R0603
U1: stm32f098rcy7; WLCSP64
U2: MAX3051EKA+T; SOT-23-8
U3: 182-009-113R531; 182-009-MALE
U4: ABLS-25.000MHZ-B2F-T
U5: ASEK-2-32.768KHz-ECST; ASEK
U6: LP3878SDX-ADJ/NOPB; WSON-8
U7: LP2954AIMX/NOPB; LP2954
U8: TPS3895ADRYR; SON-6
U9: 4-1437565-2; SW_4-1437565-2
U10: Q65110A2395; LGM67K-G1J2-24-Z
U11: nc7sz125m5x; NC7SZ125M5X

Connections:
CLK_CRYSTAL_U1_D8: C11.1, U1.D8, U4.1
CLK_CRYSTAL_U1_E8: C12.1, U1.E8, U4.2
CLK_U1_C8: U1.C8, U5.3
GND: C1.2, C2.2, C3.2, C4.2, C5.2, C6.2, C7.2, C8.2, C9.2, C10.2, C11.2, C12.2, C13.2, C14.2, C15.2, C16.2, C17.2, C18.2, C19.2, C20.2, C21.2, C22.2, C23.2, J1.2, R2.2, R5.2, R6.2, R10.2, R14.2, R17.2, R19.2, U1.A7, U1.B2, U1.G7, U1.G8, U1.H2, U2.2, U2.8, U3.5, U5.2, U6.3, U6.PAD, U7.4, U8.2, U10.C, U11.1, U11.3
NET_U1_C6: R5.1, U1.C6
NET_U1_D7: R4.1, U1.D7, U11.4
NET_U1_H4: R6.1, U1.H4
NET_U1_H7: U9.3, U9.4
NET_U1_H8: C9.1, C10.1, F1.1, U1.H8
NET_U2_6: R7.2, U2.6
NET_U3_2: R7.2, U2.6, U3.2
NET_U3_3: R7.1, U2.7, U3.3
NET_U6_1: C15.1, U6.1
NET_U6_6: R9.2, R10.1, U6.6
NET_U6_8: R8.1, U6.8
NET_U7_3: R12.1, U7.3
NET_U7_5: R11.1, U7.5
NET_U7_7: R13.2, R14.1, U7.7
NET_U8_1: R16.1, R17.1, U8.1
NET_U8_3: R18.2, R19.1, U8.3
NET_U8_4: R15.1, U8.4, U11.2
NET_U9_1: R2.1, U9.1, U9.2
PROC_CAN_RX: U1.A6, U2.4
PROC_CAN_TX: U1.B1, U2.1
VCC_S1_10V7: C16.1, C18.1, C21.1, C22.1, J1.1, R8.2, R12.2, U6.4, U7.8
VCC_TIER1_1V8: C1.1, C2.1, C3.1, C4.1, C5.1, C6.1, C7.1, C14.1, C17.1, C20.1, C23.1, F1.2, R4.2, R9.1, R15.2, R16.2, R18.1, U1.A8, U1.B8, U1.G6, U1.H1, U5.4, U6.5, U8.6, U11.5
VCC_TIER1_3V3: C8.1, C13.1, C19.1, R11.2, R13.1, U1.A1, U2.3, U7.1

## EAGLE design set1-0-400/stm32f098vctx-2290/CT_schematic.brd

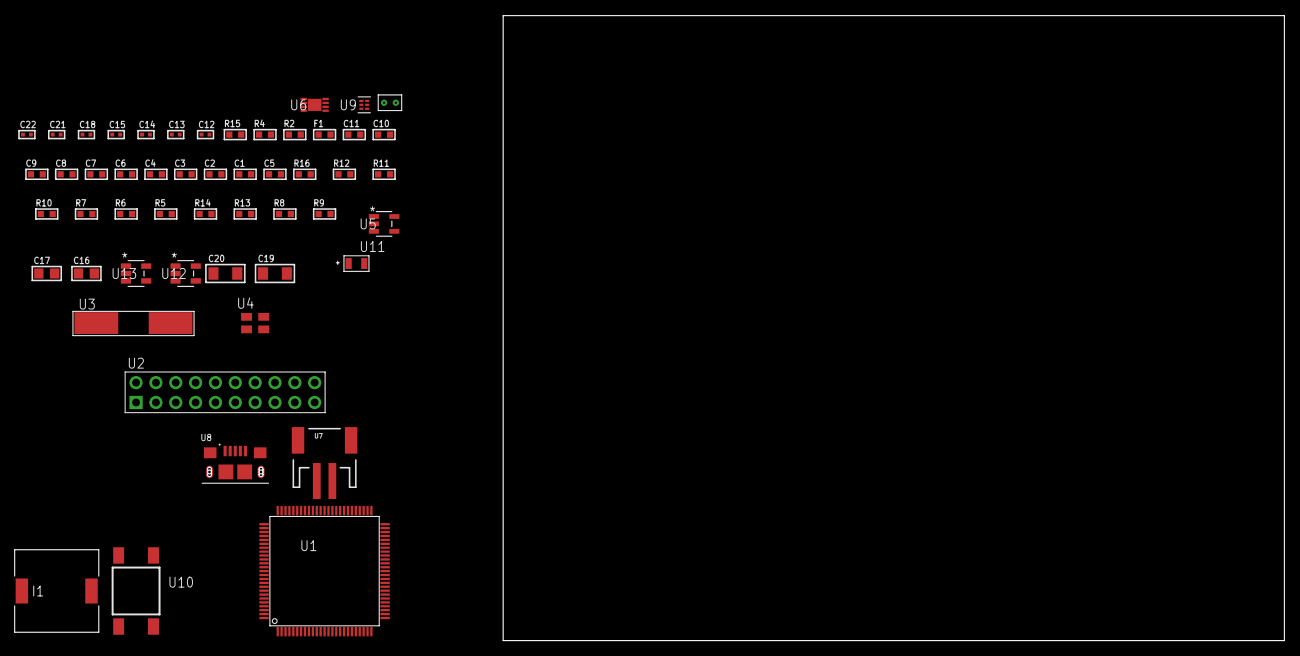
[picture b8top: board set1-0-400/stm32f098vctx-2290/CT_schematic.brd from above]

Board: 2 copper layers, 52 parts (0 on the bottom side), 25 nets, no tracks yet.

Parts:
C1, C11: 1e-06; C0603
C2, C3, C4, C6, C7, C8, C9: 1e-07; C0603
C5: 4.7e-06; C0603
C10: 1e-08; C0603
C12, C13: 1e-11; C0402
C14, C18: 1e-07; C0402
C15, C21, C22: 1e-08; C0402
C16, C17: 1e-05; C0805
C19, C20: 1e-05; C1206
F1: 240.0; L0603
I1: 5.2e-06; DR1040
R2: 1000.0; R0603
R4: 4700.0; R0603
R5, R6, R7, R10, R11, R16: 10000.0; R0603
R8: 490000.0; R0603
R9: 1000000.0; R0603
R12: 82000.0; R0603
R13: 300000.0; R0603
R14: 120000.0; R0603
R15: 2000.0; R0603
U1: stm32f098vct6; LQFP100
U2: TST-110-05-T-D-RA
U3: ABLS-25.000MHZ-B2F-T
U4: ASEK-2-32.768KHz-ECST; ASEK
U5: ltc3406es5; TSOT-23-5
U6: MCP73831T-2ACI/MC; DFN8_2X3MC
U7: S2B-PH-SM4-TB(LF)(SN); JST-2-SMD
U8: 10118193-0001LF; FCI_10118193-0001LF
U9: TPS3895ADRYR; SON-6
U10: 4-1437565-2; SW_4-1437565-2
U11: Q65110A2395; LGM67K-G1J2-24-Z
U12, U13: nc7sz125m5x; NC7SZ125M5X
U14: Dummy; DUMMY_PACKAGE_113

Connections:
CLK_CRYSTAL_U1_12: C12.1, U1.12, U3.1
CLK_CRYSTAL_U1_13: C13.1, U1.13, U3.2
CLK_U1_8: U1.8, U4.3
GND: C1.2, C2.2, C3.2, C4.2, C5.2, C6.2, C7.2, C8.2, C9.2, C10.2, C11.2, C12.2, C13.2, C14.2, C15.2, C16.2, C17.1, C17.2, C18.2, C19.2, C20.2, C21.2, C22.2, R2.2, R5.2, R6.2, R8.2, R12.2, R14.2, R15.2, U1.20, U1.27, U1.49, U1.74, U1.99, U2.4, U2.6, U2.8, U2.10, U2.12, U2.14, U2.16, U2.18, U2.20, U4.2, U5.2, U6.6, U6.9, U7.2, U8.5, U8.6, U8.7, U8.8, U8.9, U9.2, U11.C, U12.2, U12.3, U13.1, U13.3, U14.1
INPUT_USBPOWER_5V: C19.1, R16.2, U6.1, U6.2, U8.1
NET_U1_14: R4.1, U1.14, U13.4
NET_U1_21: C10.1, C11.1, F1.1, U1.21
NET_U1_37: R6.1, U1.37
NET_U1_94: R5.1, U1.94
NET_U1_98: U10.3, U10.4
NET_U5_3: I1.1, U5.3
NET_U5_5: R8.1, R9.1, U5.5
NET_U5_ATNET_3: I1.2, R9.2
NET_U6_5: R16.1, U6.5
NET_U6_8: R15.1, U6.8
NET_U9_1: R11.1, R12.1, U9.1
NET_U9_3: R13.2, R14.1, U9.3
NET_U9_4: R10.1, U9.4, U12.4, U13.2
NET_U10_1: R2.1, U10.1, U10.2
PROC_DAC_OUT2: U1.30, U14.2
PROC_SYS_SWCLK: U1.76, U2.9
PROC_SYS_SWDIO: U1.72, U2.7
RST_OUT_U2_SRESET_B: R7.1, U2.15, U12.1
VCC_S1_3V7: C16.1, C20.1, U5.4, U6.3, U6.4, U7.1
VCC_TIER1_1V8: C1.1, C2.1, C3.1, C4.1, C5.1, C6.1, C7.1, C8.1, C9.1, C14.1, C15.1, C17.2, C18.1, C21.1, C22.1, F1.2, I1.2, R4.2, R7.2, R9.2, R10.2, R11.2, R13.1, U1.6, U1.28, U1.50, U1.75, U1.100, U2.1, U4.4, U9.6, U12.5, U13.5

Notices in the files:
parts and their libraries:
circuit_tree: (C) 2014 Tomasz Boleslaw CEDRO, cederom@tlen.pl, http://www.tomek.cedro.info.
